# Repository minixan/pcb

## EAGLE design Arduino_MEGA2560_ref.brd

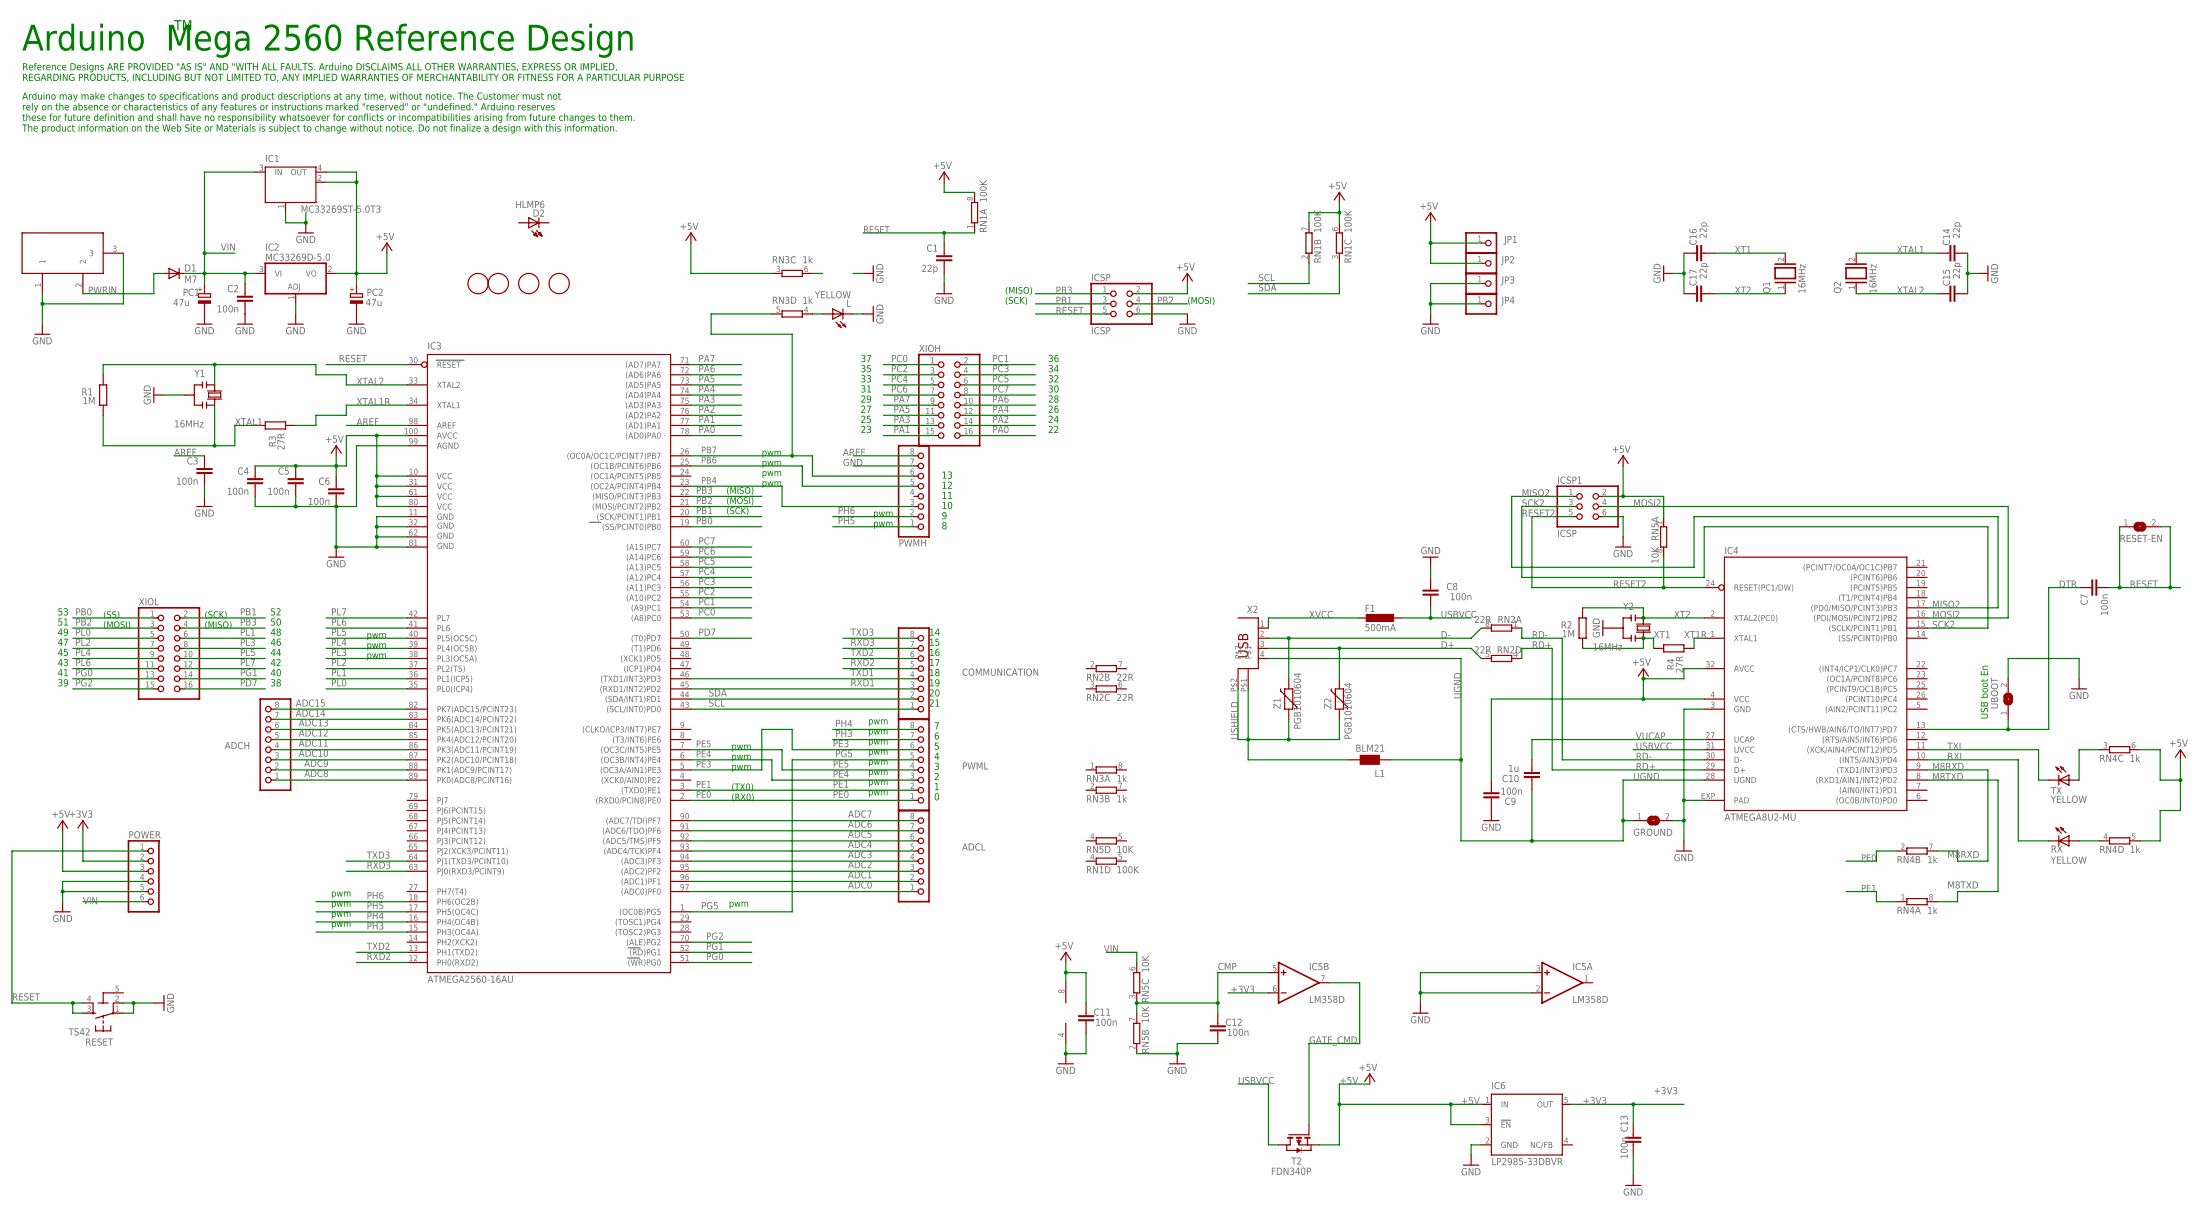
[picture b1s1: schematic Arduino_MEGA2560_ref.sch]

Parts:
ADCH: PINHD-1X8; 1X08
ADCL: PINHD-1X8; 1X08
C1, C14, C15, C16, C17: 22p; C0603-ROUND
C2, C3, C4, C5, C6, C7, C9, C12, C13: 100n; C0603-ROUND
C8, C11: 100n; C0603
C10: 1u; C0603-ROUND
COMMUNICATION: PINHD-1X8; 1X08
D1: M7; SMB
D2: HLMP6
F1: 500mA; L1812
GROUND: SJ
IC1: MC33269ST-5.0T3; SOT223
IC2: MC33269D-5.0; DPACK
IC3: ATMEGA2560-16AU; TQFP100
IC4: ATMEGA8U2-MU; QFN32
IC5: LM358D; SO08
IC6: LP2985-33DBVR; SOT23-DBV
ICSP, ICSP1: ICSP; 2X03
JP1, JP2, JP3, JP4: PINHD-1X1; 1X01
L: YELLOW; CHIP-LED0805
L1: BLM21; 0805
PC1, PC2: 47u; PANASONIC_D
POWER: PINHD-1X6; 1X06
PWMH: PINHD-1X8; 1X08
PWML: PINHD-1X8; 1X08
Q1, Q2: 16MHz; QS
R1, R2: 1M; R0603-ROUND
R3, R4: 27R; R0603-ROUND
RESET: TS42
RESET-EN: SJ
RN1: 100K; CAT16
RN2: 22R; CAY16
RN3, RN4: 1k; CAY16
RN5: 10K; CAT16
RX: YELLOW; CHIP-LED0805
T2: FDN340P; SOT-23
TX: YELLOW; CHIP-LED0805
U$2, U$3, U$4, U$5: FIDUCIALMOUNT; FIDUCIA-MOUNT
UBOOT: SJ
X1: DC21MMX; DC-21MM
X2: PN61729
XIOH: PINHD-2X8; 2X08
XIOL: PINHD-2X8; 2X08
Y1, Y2: 16MHz; RESONATOR
Z1, Z2: PGB1010604; CT/CN0603

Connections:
5-GND: RESET.5 (5-GND)
+3V3: C13.2, IC5.6 (-IN), IC6.5 (OUT), POWER.2
+5V: C4.1, C5.1, C6.1, C9.1, C11.2, IC1.2 (OUT), IC1.4 (OUT), IC2.2 (VO), IC3.10 (VCC), IC3.31 (VCC1), IC3.61 (VCC2), IC3.80 (VCC3), IC3.100 (AVCC), IC4.4 (VCC), IC4.32 (AVCC), IC5.8 (V+), IC6.1 (IN), IC6.3 (!EN), ICSP.2, ICSP1.2, JP1.1, JP2.1, PC2.+, POWER.3, RN1.6 (2), RN1.7 (2), RN1.8 (2), RN3.3 (1), RN4.5 (2), RN4.6 (2), RN5.1, T2.2 (S)
ADC0: ADCL.1, IC3.97 ((ADC0)PF0)
ADC1: ADCL.2, IC3.96 ((ADC1)PF1)
ADC2: ADCL.3, IC3.95 ((ADC2)PF2)
ADC3: ADCL.4, IC3.94 ((ADC3)PF3)
ADC4: ADCL.5, IC3.93 ((ADC4/TCK)PF4)
ADC5: ADCL.6, IC3.92 ((ADC5/TMS)PF5)
ADC6: ADCL.7, IC3.91 ((ADC6/TDO)PF6)
ADC7: ADCL.8, IC3.90 ((ADC7/TDI)PF7)
ADC8: ADCH.1, IC3.89 (PK0(ADC8/PCINT16))
ADC9: ADCH.2, IC3.88 (PK1(ADC9/PCINT17))
ADC10: ADCH.3, IC3.87 (PK2(ADC10/PCINT18))
ADC11: ADCH.4, IC3.86 (PK3(ADC11/PCINT19))
ADC12: ADCH.5, IC3.85 (PK4(ADC12/PCINT20))
ADC13: ADCH.6, IC3.84 (PK5(ADC13/PCINT21))
ADC14: ADCH.7, IC3.83 (PK6(ADC14/PCINT22))
ADC15: ADCH.8, IC3.82 (PK7(ADC15/PCINT23))
AREF: C3.1, IC3.98 (AREF), PWMH.8
CMP: C12.2, IC5.5 (+IN), RN5.3 (1), RN5.7 (2)
D+: RN2.5 (2), X2.3, Z2.2
D-: RN2.8 (2), X2.2, Z1.2
DTR: C7.1, IC4.13 ((CTS/HWB/AIN6/TO/INT7)PD7), UBOOT.1
GATE_CMD: IC5.7 (OUT), T2.3 (G)
GND: C1.2, C2.2, C3.2, C4.2, C5.2, C6.2, C8.2, C9.2, C11.1, C12.1, C13.1, C14.1, C15.1, C16.2, C17.2, GROUND.2, IC1.1 (GND/ADJ), IC2.1 (ADJ), IC3.11 (GND), IC3.32 (GND1), IC3.62 (GND2), IC3.81 (GND3), IC3.99 (AGND), IC4.3 (GND), IC4.EXP (PAD), IC5.2 (-IN), IC5.3 (+IN), IC5.4 (V-), IC6.2 (GND), ICSP.6, ICSP1.6, JP3.1, JP4.1, L.C, PC1.-, PC2.-, POWER.4, POWER.5, PWMH.7, RESET.1, RESET.2, RN5.2 (1), UBOOT.2, X1.1, X1.3, Y1.2, Y2.2
M8RXD: IC4.9 ((TXD1/INT3)PD3), RN4.7 (2)
M8TXD: IC4.8 ((RXD1/AIN1/INT2)PD2), RN4.8 (2)
MISO2: IC4.17 ((PD0/MISO/PCINT3)PB3), ICSP1.1
MOSI2: IC4.16 ((PDI/MOSI/PCINT2)PB2), ICSP1.4
unnamed: L.A, RN3.4 (1)
unnamed: RN4.4 (1), RX.A
unnamed: RN4.3 (1), TX.A
PA0: IC3.78 ((AD0)PA0), XIOH.16
PA1: IC3.77 ((AD1)PA1), XIOH.15
PA2: IC3.76 ((AD2)PA2), XIOH.14
PA3: IC3.75 ((AD3)PA3), XIOH.13
PA4: IC3.74 ((AD4)PA4), XIOH.12
PA5: IC3.73 ((AD5)PA5), XIOH.11
PA6: IC3.72 ((AD6)PA6), XIOH.10
PA7: IC3.71 ((AD7)PA7), XIOH.9
PB0: IC3.19 ((SS/PCINT0)PB0), XIOL.1
PB1: IC3.20 ((SCK/PCINT1)PB1), ICSP.3, XIOL.2
PB2: IC3.21 ((MOSI/PCINT2)PB2), ICSP.4, XIOL.3
PB3: IC3.22 ((MISO/PCINT3)PB3), ICSP.1, XIOL.4
PB4: IC3.23 ((OC2A/PCINT4)PB4), PWMH.3
PB6: IC3.25 ((OC1B/PCINT6)PB6), PWMH.5
PB7: IC3.26 ((OC0A/OC1C/PCINT7)PB7), PWMH.6, RN3.5 (2)
PC0: IC3.53 ((A8)PC0), XIOH.1
PC1: IC3.54 ((A9)PC1), XIOH.2
PC2: IC3.55 ((A10)PC2), XIOH.3
PC3: IC3.56 ((A11)PC3), XIOH.4
PC4: IC3.57 ((A12)PC4), XIOH.5
PC5: IC3.58 ((A13)PC5), XIOH.6
PC6: IC3.59 ((A14)PC6), XIOH.7
PC7: IC3.60 ((A15)PC7), XIOH.8
PD7: IC3.50 ((T0)PD7), XIOL.16
PE0: IC3.2 ((RXD0/PCIN8)PE0), PWML.1, RN4.2 (1)
PE1: IC3.3 ((TXD0)PE1), PWML.2, RN4.1
PE3: IC3.5 ((OC3A/AIN1)PE3), PWML.6
PE4: IC3.6 ((OC3B/INT4)PE4), PWML.3
PE5: IC3.7 ((OC3C/INT5)PE5), PWML.4
PG0: IC3.51 ((WR)PG0), XIOL.13
PG1: IC3.52 ((RD)PG1), XIOL.14
PG2: IC3.70 ((ALE)PG2), XIOL.15
PG5: IC3.1 ((OC0B)PG5), PWML.5
PH3: IC3.15 (PH3(OC4A)), PWML.7
PH4: IC3.16 (PH4(OC4B)), PWML.8
PH5: IC3.17 (PH5(OC4C)), PWMH.1
PH6: IC3.18 (PH6(OC2B)), PWMH.2
PL0: IC3.35 (PL0(ICP4)), XIOL.5
PL1: IC3.36 (PL1(ICP5)), XIOL.6
PL2: IC3.37 (PL2(T5)), XIOL.7
PL3: IC3.38 (PL3(OC5A)), XIOL.8
PL4: IC3.39 (PL4(OC5B)), XIOL.9
PL5: IC3.40 (PL5(OC5C)), XIOL.10
PL6: IC3.41 (PL6), XIOL.11
PL7: IC3.42 (PL7), XIOL.12
PWRIN: D1.A, X1.2
RD+: IC4.29 (D+), RN2.4 (1)
RD-: IC4.30 (D-), RN2.1
RESET: C1.1, C7.2, IC3.30 (RESET), ICSP.5, POWER.1, RESET.3, RESET.4, RESET-EN.1, RESET-EN.2, RN1.1
RESET2: IC4.24 (RESET(PC1/DW)), ICSP1.5, RN5.8 (2)
RXD1: COMMUNICATION.3, IC3.45 ((RXD1/INT2)PD2)
RXD2: COMMUNICATION.5, IC3.12 (PH0(RXD2))
RXD3: COMMUNICATION.7, IC3.63 (PJ0(RXD3/PCINT9))
RXL: IC4.10 ((INT5/AIN3)PD4), RX.C
SCK2: IC4.15 ((SCLK/PCINT1)PB1), ICSP1.3
SCL: COMMUNICATION.1, IC3.43 ((SCL/INT0)PD0), RN1.2 (1)
SDA: COMMUNICATION.2, IC3.44 ((SDA/INT1)PD1), RN1.3 (1)
TXD1: COMMUNICATION.4, IC3.46 ((TXD1/INT3)PD3)
TXD2: COMMUNICATION.6, IC3.13 (PH1(TXD2))
TXD3: COMMUNICATION.8, IC3.64 (PJ1(TXD3/PCINT10))
TXL: IC4.11 ((XCK/AIN4/PCINT12)PD5), TX.C
UGND: C10.2, GROUND.1, IC4.28 (UGND), L1.1, X2.4
USBVCC: C8.1, F1.1, IC4.31 (UVCC), T2.1 (D)
USHIELD: L1.2, X2.P$1, X2.P$2, Z1.1, Z2.1
VIN: C2.1, D1.C, IC1.3 (IN), IC2.3 (VI), PC1.+, POWER.6, RN5.6 (2)
VUCAP: C10.1, IC4.27 (UCAP)
XT1: C16.1, Q1.2, R2.1, R4.2, Y2.3
XT1R: IC4.1 (XTAL1), R4.1
XT2: C17.1, IC4.2 (XTAL2(PC0)), Q1.1, R2.2, Y2.1
XTAL1: C14.2, Q2.2, R1.1, R3.2, Y1.3
XTAL1R: IC3.34 (XTAL1), R3.1
XTAL2: C15.2, IC3.33 (XTAL2), Q2.1, R1.2, Y1.1
XVCC: F1.2, X2.1

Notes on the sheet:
(SCK)
(MISO)
(MOSI)
pwm
(TX0)
(RX0)
(SS)
USB boot En
Arduino Mega 2560 Reference Design
Arduino may make changes to specifications and product descriptions at any time, without notice. The Customer must not rely on the absence or characteristics of any features or instructions marked "reserved" or "undefined." Arduino reserves these for future definition and shall have no responsibili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
Reference Designs ARE PROVIDED "AS IS" AND "WITH ALL FAULTS. Arduino DISCLAIMS ALL OTHER WARRANTIES, EXPRESS OR IMPLIED, REGARDING PRODUCTS, INCLUDING BUT NOT LIMITED TO, ANY IMPLIED WARRANTIES OF MERCHANTABILITY OR FITNESS FOR A PARTICULAR PURPOSE

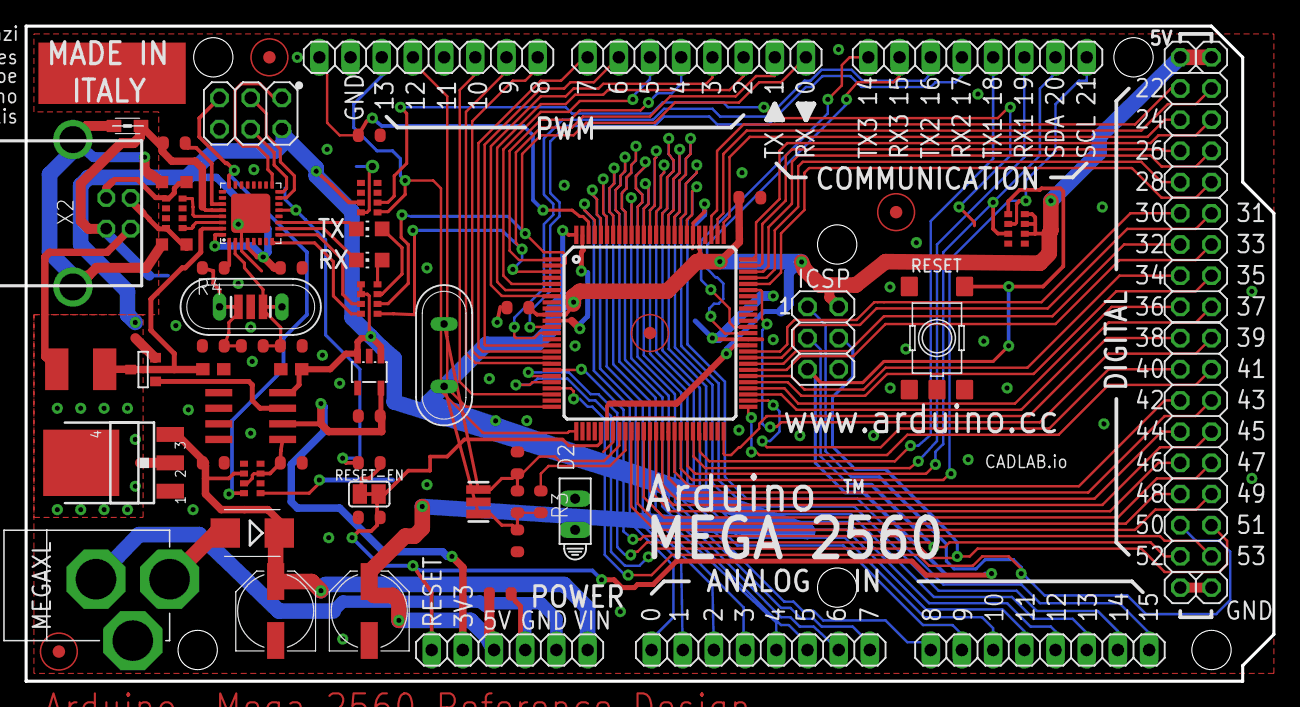
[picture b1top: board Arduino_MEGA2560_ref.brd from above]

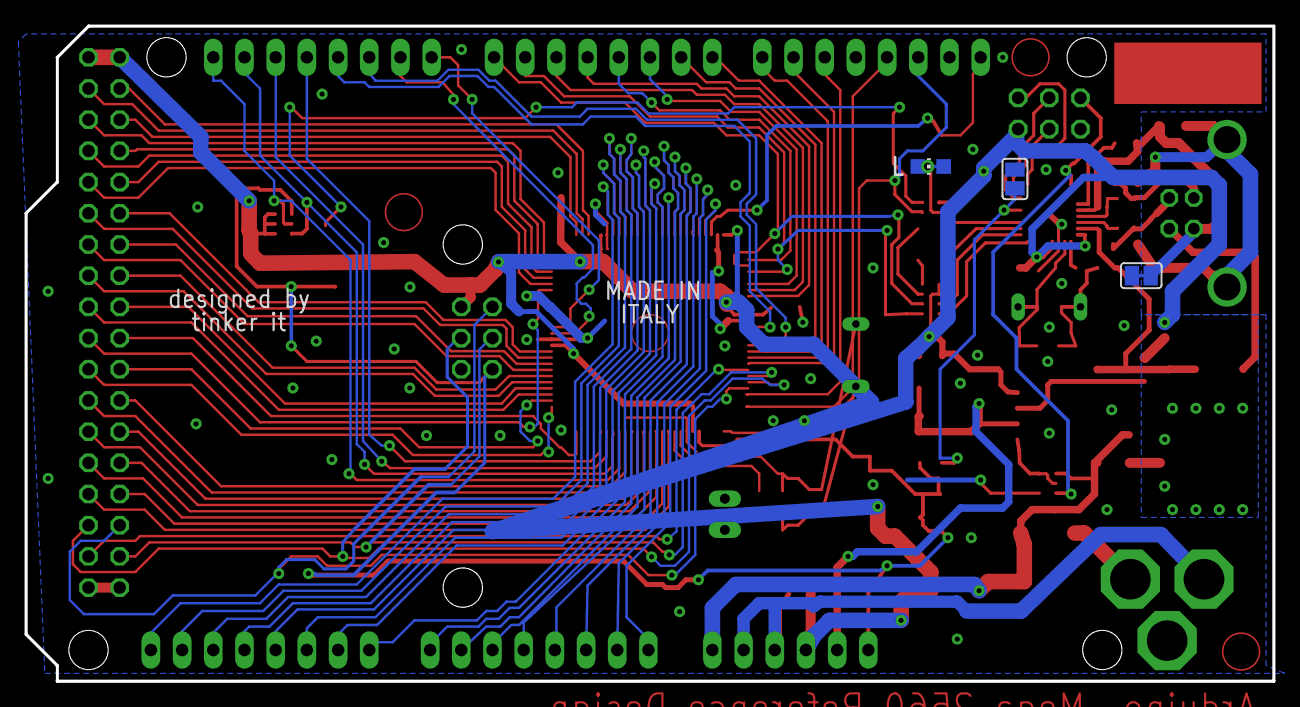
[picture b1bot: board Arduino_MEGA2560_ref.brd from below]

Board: 2 copper layers, 101.6 x 53.3 mm, 72 parts (3 on the bottom side), 105 nets.

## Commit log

2017-08-22 files added
2017-08-22 bus moved
2017-08-22 develop changes
2017-08-22 master changes
2017-08-22 feature branch created with some changes
